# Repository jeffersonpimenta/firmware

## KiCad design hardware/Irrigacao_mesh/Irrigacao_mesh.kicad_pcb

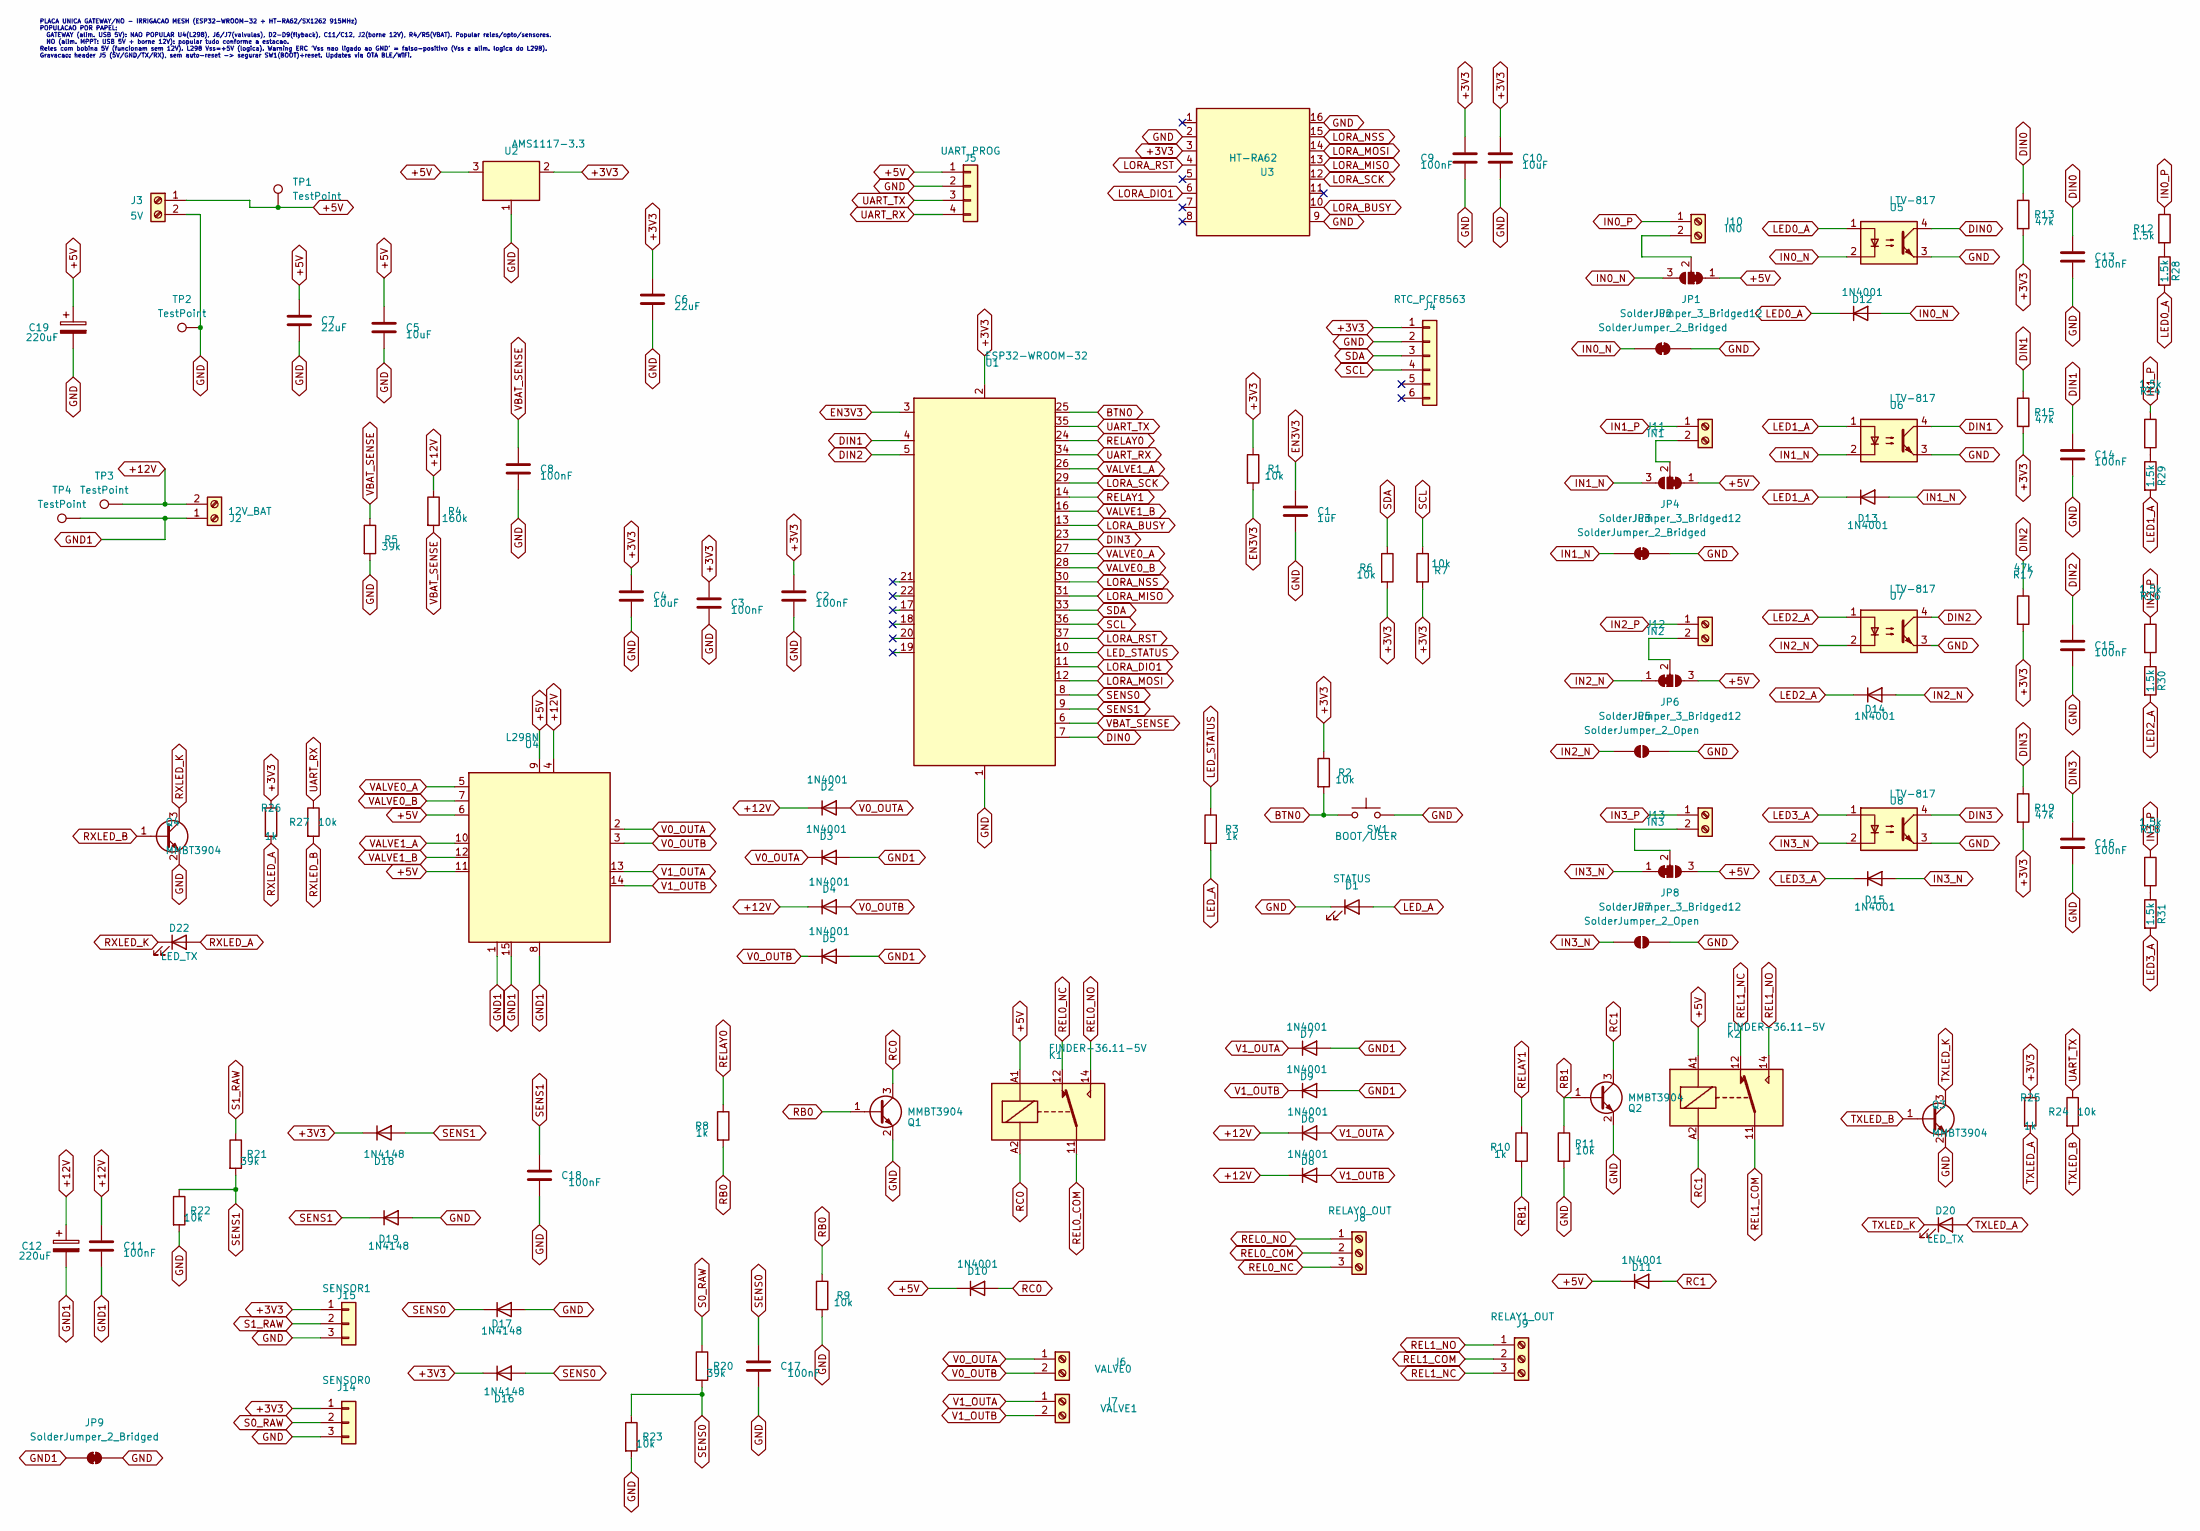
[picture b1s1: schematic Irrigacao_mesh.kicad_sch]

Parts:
C1: 1uF; C_0805_2012Metric
C2, C3, C8, C9, C11, C13, C14, C15, C16, C17, C18: 100nF; C_0805_2012Metric
C4, C5, C10: 10uF; C_0805_2012Metric
C6: 22uF; C_0805_2012Metric
C7: 22uF; C_0805_2012Metric; Voltage 25V; LCSC C45783
C12, C19: 220uF; CP_Elec_8x10.5; Voltage 25V; LCSC C129421
D1: STATUS; LED_0805_2012Metric
D2, D3, D4, D5, D6, D7, D8, D9, D10, D11, D12, D13, D14, D15: 1N4001; D_SMA
D16, D17, D18, D19: 1N4148; D_SOD-123
D20, D22: LED_TX; LED_0805_2012Metric
J2: 12V_BAT; TerminalBlock_MaiXu_MX126-5.0-02P_1x02_P5.00mm
J3: 5V; TerminalBlock_MaiXu_MX126-5.0-02P_1x02_P5.00mm
J4: RTC_PCF8563; PinHeader_1x06_P2.54mm_Vertical
J5: UART_PROG; PinHeader_1x04_P2.54mm_Vertical
J6: VALVE0; TerminalBlock_MaiXu_MX126-5.0-02P_1x02_P5.00mm
J7: VALVE1; TerminalBlock_MaiXu_MX126-5.0-02P_1x02_P5.00mm
J8: RELAY0_OUT; TerminalBlock_MaiXu_MX126-5.0-03P_1x03_P5.00mm
J9: RELAY1_OUT; TerminalBlock_MaiXu_MX126-5.0-03P_1x03_P5.00mm
J10: IN0; TerminalBlock_MaiXu_MX126-5.0-02P_1x02_P5.00mm
J11: IN1; TerminalBlock_MaiXu_MX126-5.0-02P_1x02_P5.00mm
J12: IN2; TerminalBlock_MaiXu_MX126-5.0-02P_1x02_P5.00mm
J13: IN3; TerminalBlock_MaiXu_MX126-5.0-02P_1x02_P5.00mm
J14: SENSOR0; PinHeader_1x03_P2.54mm_Vertical
J15: SENSOR1; PinHeader_1x03_P2.54mm_Vertical
JP1, JP4, JP6, JP8: SolderJumper_3_Bridged12; SolderJumper-3_P1.3mm_Bridged12_Pad1.0x1.5mm_NumberLabels
JP2, JP3, JP9: SolderJumper_2_Bridged; SolderJumper-2_P1.3mm_Bridged_Pad1.0x1.5mm
JP5, JP7: SolderJumper_2_Open; SolderJumper-2_P1.3mm_Open_Pad1.0x1.5mm
K1, K2: FINDER-36.11-5V; Relay_SPDT_Finder_36.11
Q1, Q2, Q3, Q4: MMBT3904; SOT-23
R1, R2, R9, R11, R22, R23, R24, R27: 10k; R_0805_2012Metric
R3, R25, R26: 1k; R_0805_2012Metric; LCSC C17513
R4: 160k; R_0603_1608Metric; LCSC C22813
R5: 39k; R_0603_1608Metric; LCSC C23153
R6, R7: 10k; R_0805_2012Metric; LCSC C17414
R8, R10: 1k; R_0805_2012Metric
R12, R14, R16, R18, R28, R29, R30, R31: 1.5k; R_0805_2012Metric
R13, R15, R17, R19: 47k; R_0805_2012Metric
R20, R21: 39k; R_0603_1608Metric
SW1: BOOT/USER; SW_Push_1P1T_XKB_TS-1187A
TP1, TP2, TP3, TP4: TestPoint; TestPoint_Pad_D4.0mm
U1: ESP32-WROOM-32
U2: AMS1117-3.3; SOT-223-3_TabPin2
U3: HT-RA62
U4: L298N; TO-220-15_P2.54x5.08mm_StaggerOdd_Lead4.58mm_Vertical
U5, U6, U7, U8: LTV-817; SMDIP-4_W7.62mm

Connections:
+3V3: C2.1, C3.1, C4.1, C6.1, C9.1, C10.1, D16.1 (K), D18.1 (K), J4.1, J14.1, J15.1, R1.1, R2.1, R6.2, R7.2, R13.2, R15.2, R17.2, R19.2, R25.1, R26.1, U1.2 (VDD), U2.2 (VO), U3.3 (3V3)
+5V: C5.1, C7.1, C19.1, D10.1 (K), D11.1 (K), J3.1, J5.1, JP1.1 (A), JP4.1 (A), JP6.3 (B), JP8.3 (B), K1.A1, K2.A1, TP1.1 (1_1), U2.3 (VI), U4.6 (EnA), U4.9 (Vss), U4.11 (EnB)
+12V: C11.1, C12.1, D2.1 (K), D4.1 (K), D6.1 (K), D8.1 (K), J2.2, R4.1, TP3.1 (1_1), U4.4 (Vs)
BTN0: R2.2, SW1.1, U1.25 (IO0)
DIN0: C13.1, R13.1, U1.7 (IO35), U5.4
DIN1: C14.1, R15.1, U1.4 (SENSOR_VP), U6.4
DIN2: C15.1, R17.1, U1.5 (SENSOR_VN), U7.4
DIN3: C16.1, R19.1, U1.23 (IO15), U8.4
EN3V3: C1.1, R1.2, U1.3 (EN)
GND: C1.2, C2.2, C3.2, C4.2, C5.2, C6.2, C7.2, C8.2, C9.2, C10.2, C13.2, C14.2, C15.2, C16.2, C17.2, C18.2, C19.2, D1.1 (K), D17.2 (A), D19.2 (A), J3.2, J4.2, J5.2, J14.3, J15.3, JP2.2 (B), JP3.2 (B), JP5.2 (B), JP7.2 (B), JP9.2 (B), Q1.2 (E), Q2.2 (E), Q3.2 (E), Q4.2 (E), R5.2, R9.2, R11.2, R22.2, R23.2, SW1.2, TP2.1 (1_1), U1.1 (GND), U1.15 (GND), U1.38 (GND), U1.39 (GND), U2.1 (GND), U3.2 (GND), U3.9 (GND), U3.16 (GND), U5.3, U6.3, U7.3, U8.3
GND1: C11.2, C12.2, D3.2 (A), D5.2 (A), D7.2 (A), D9.2 (A), J2.1, JP9.1 (A), TP4.1 (1_1), U4.1 (SENSE_A), U4.8 (GND), U4.15 (SENSE_B)
IN0_N: D12.2 (A), JP1.3 (B), JP2.1 (A), U5.2
IN0_P: J10.1, R12.1
IN1_N: D13.2 (A), JP3.1 (A), JP4.3 (B), U6.2
IN1_P: J11.1, R14.1
IN2_N: D14.2 (A), JP5.1 (A), JP6.1 (A), U7.2
IN2_P: J12.1, R16.1
IN3_N: D15.2 (A), JP7.1 (A), JP8.1 (A), U8.2
IN3_P: J13.1, R18.1
LED0_A: D12.1 (K), R28.2, U5.1
LED1_A: D13.1 (K), R29.2, U6.1
LED2_A: D14.1 (K), R30.2, U7.1
LED3_A: D15.1 (K), R31.2, U8.1
LED_A: D1.2 (A), R3.2
LED_STATUS: R3.1, U1.10 (IO25)
LORA_BUSY: U1.13 (IO14), U3.10 (BUSY)
LORA_DIO1: U1.11 (IO26), U3.6 (DIO1)
LORA_MISO: U1.31 (IO19), U3.13 (MISO)
LORA_MOSI: U1.12 (IO27), U3.14 (MOSI)
LORA_NSS: U1.30 (IO18), U3.15 (NSS)
LORA_RST: U1.37 (IO23), U3.4 (RST)
LORA_SCK: U1.29 (IO5), U3.12 (SCK)
unnamed: J10.2, JP1.2 (C)
unnamed: J11.2, JP4.2 (C)
unnamed: J12.2, JP6.2 (C)
unnamed: J13.2, JP8.2 (C)
unnamed: R12.2, R28.1
unnamed: R14.2, R29.1
unnamed: R16.2, R30.1
unnamed: R18.2, R31.1
RB0: Q1.1 (B), R8.2, R9.1
RB1: Q2.1 (B), R10.2, R11.1
RC0: D10.2 (A), K1.A2, Q1.3 (C)
RC1: D11.2 (A), K2.A2, Q2.3 (C)
REL0_COM: J8.2, K1.11
REL0_NC: J8.3, K1.12
REL0_NO: J8.1, K1.14
REL1_COM: J9.2, K2.11
REL1_NC: J9.3, K2.12
REL1_NO: J9.1, K2.14
RELAY0: R8.1, U1.24 (IO2)
RELAY1: R10.1, U1.14 (IO12)
RXLED_A: D22.2 (A), R26.2
RXLED_B: Q4.1 (B), R27.2
RXLED_K: D22.1 (K), Q4.3 (C)
S0_RAW: J14.2, R20.1
S1_RAW: J15.2, R21.1
SCL: J4.4, R7.1, U1.36 (IO22)
SDA: J4.3, R6.1, U1.33 (IO21)
SENS0: C17.1, D16.2 (A), D17.1 (K), R20.2, R23.1, U1.8 (IO32)
SENS1: C18.1, D18.2 (A), D19.1 (K), R21.2, R22.1, U1.9 (IO33)
TXLED_A: D20.2 (A), R25.2
TXLED_B: Q3.1 (B), R24.2
TXLED_K: D20.1 (K), Q3.3 (C)
UART_RX: J5.4, R27.1, U1.34 (RXD0/IO3)
UART_TX: J5.3, R24.1, U1.35 (TXD0/IO1)
V0_OUTA: D2.2 (A), D3.1 (K), J6.1, U4.2 (OUT1)
V0_OUTB: D4.2 (A), D5.1 (K), J6.2, U4.3 (OUT2)
V1_OUTA: D6.2 (A), D7.1 (K), J7.1, U4.13 (OUT3)
V1_OUTB: D8.2 (A), D9.1 (K), J7.2, U4.14 (OUT4)
VALVE0_A: U1.27 (IO16), U4.5 (IN1)
VALVE0_B: U1.28 (IO17), U4.7 (IN2)
VALVE1_A: U1.26 (IO4), U4.10 (IN3)
VALVE1_B: U1.16 (IO13), U4.12 (IN4)
VBAT_SENSE: C8.1, R4.2, R5.1, U1.6 (IO34)

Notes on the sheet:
PLACA UNICA GATEWAY/NO - IRRIGACAO MESH (ESP32-WROOM-32 + HT-RA62/SX1262 915MHz) POPULACAO POR PAPEL: GATEWAY (alim. USB 5V): NAO POPULAR U4(L298), J6/J7(valvulas), D2-D9(flyback), C11/C12, J2(borne 12V), R4/R5(VBAT). Popular reles/opto/sensores. NO (alim. MPPT: USB 5V + borne 12V): popular tudo co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

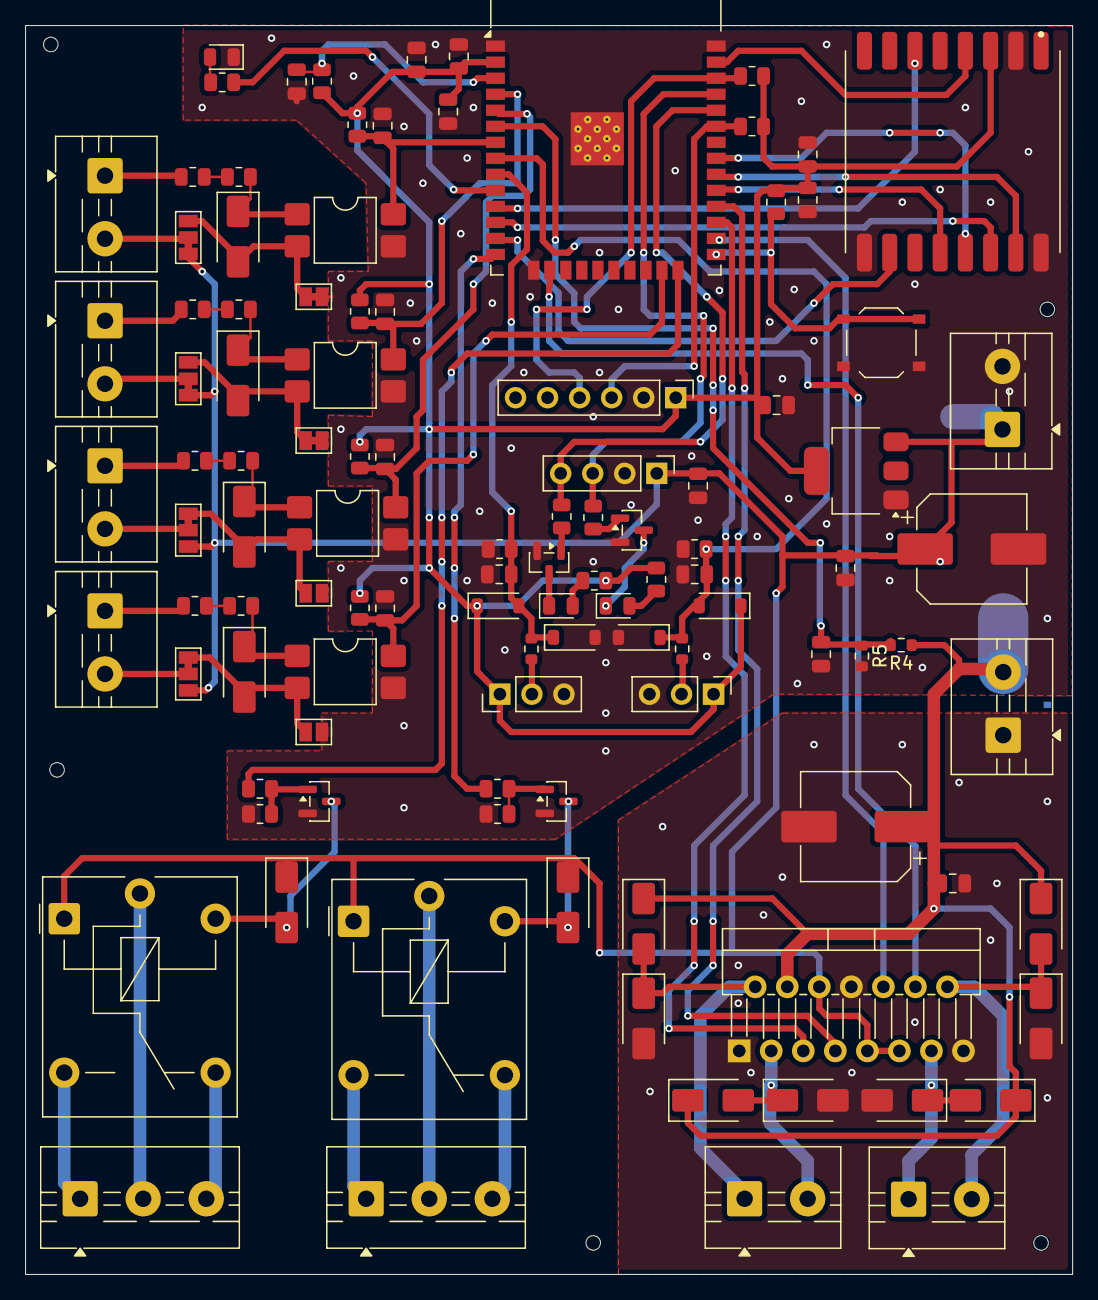
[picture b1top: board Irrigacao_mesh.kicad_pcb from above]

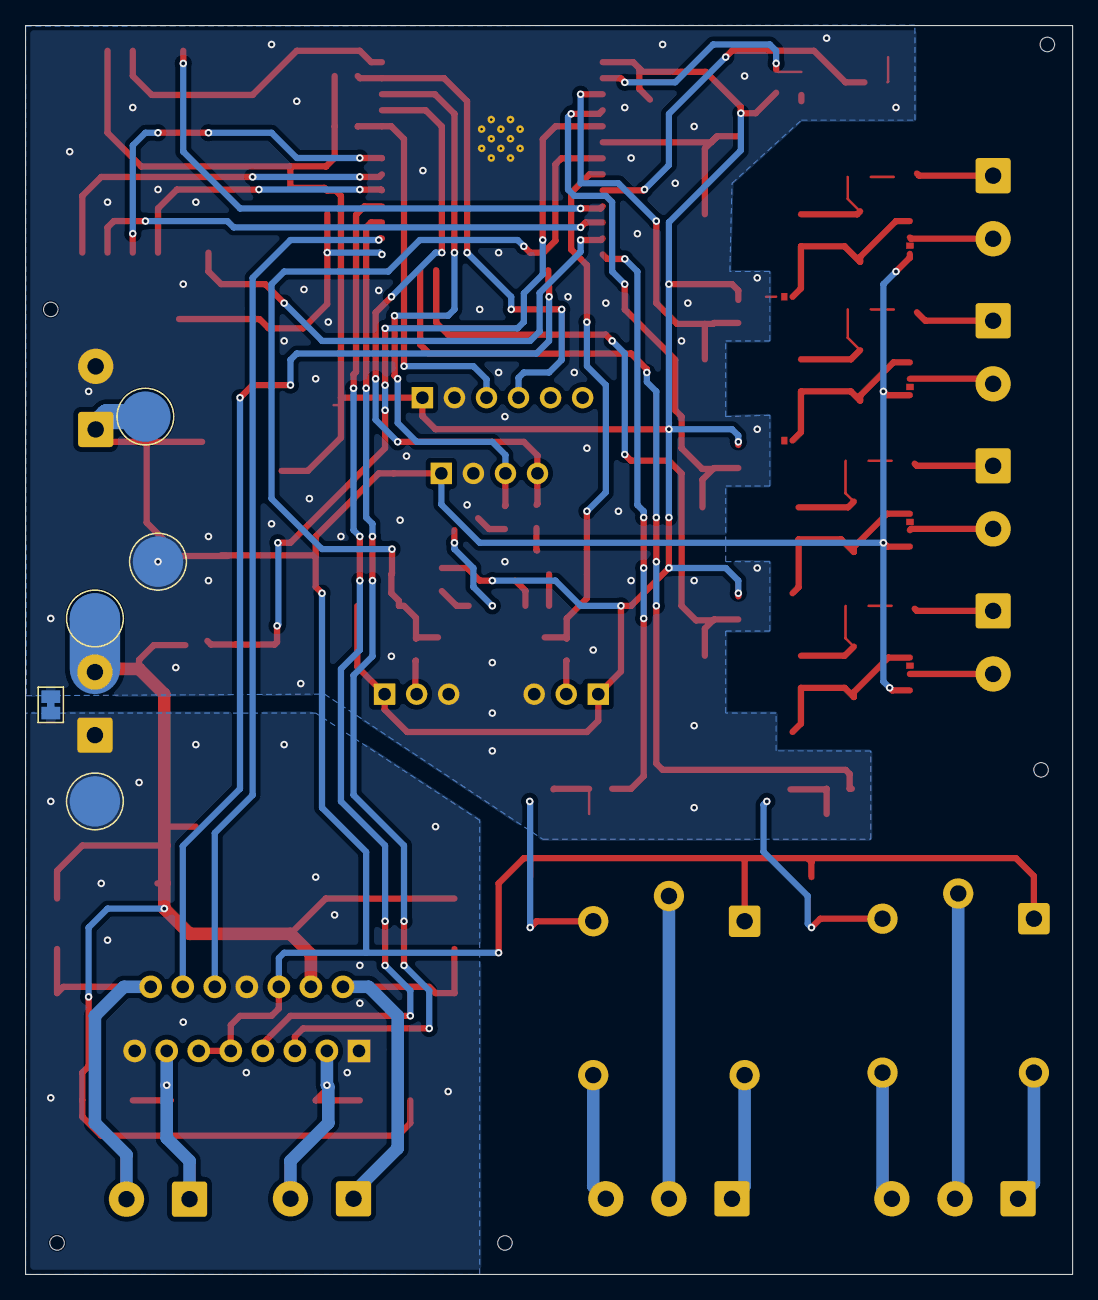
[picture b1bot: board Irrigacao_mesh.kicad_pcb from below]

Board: 2 copper layers, 83.0 x 99.0 mm, 113 parts (5 on the bottom side), 75 nets.

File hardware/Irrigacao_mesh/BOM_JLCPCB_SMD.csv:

Comment,Designator,Footprint,LCSC Part #
10k,"R1,R2,R6,R7,R9,R11,R22,R23,R24,R27",R0805,C17414
47k,"R13,R15,R17,R19",R0805,C17713
1k,"R3,R8,R10,R25,R26",R0805,C17513
1.5k,"R12,R14,R16,R18,R28,R29,R30,R31",R0805,C4310
160k,"R4",R0603,C22813
39k,"R5,R20,R21",R0603,C23153
100nF 50V,"C2,C3,C8,C9,C11,C13,C14,C15,C16,C17,C18",C0805,C49678
1uF 50V,"C1",C0805,C28323
10uF 25V,"C4,C5,C10",C0805,C15850
22uF 25V,"C6,C7",C0805,C45783
220uF 25V,"C12,C19",CP_Elec_8x10.5,C129421
1N4001 / M7,"D2,D3,D4,D5,D6,D7,D8,D9,D10,D11,D12,D13,D14,D15",D_SMA,C95872
1N4148W,"D16,D17,D18,D19",SOD-123,C81598
LED vermelho 0805,"D1,D20,D22",LED0805,C84256
MMBT3904,"Q1,Q2,Q3,Q4",SOT-23,C20526
AMS1117-3.3,"U2",SOT-223,C6186
LTV-817S,"U5,U6,U7,U8",SMDIP-4_W7.62mm,C109227
TS-1187A tactile,"SW1",SW_Push_1P1T_XKB_TS-1187A,C318884

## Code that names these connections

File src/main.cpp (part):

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#if defined(RAK3401) || defined(RAK13302)
    pinMode(WB_IO2, OUTPUT);
    digitalWrite(WB_IO2, HIGH);
    SPI1.setPins(LORA_MISO, LORA_SCK, LORA_MOSI);
    SPI1.begin();
#else
    SPI.begin();
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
